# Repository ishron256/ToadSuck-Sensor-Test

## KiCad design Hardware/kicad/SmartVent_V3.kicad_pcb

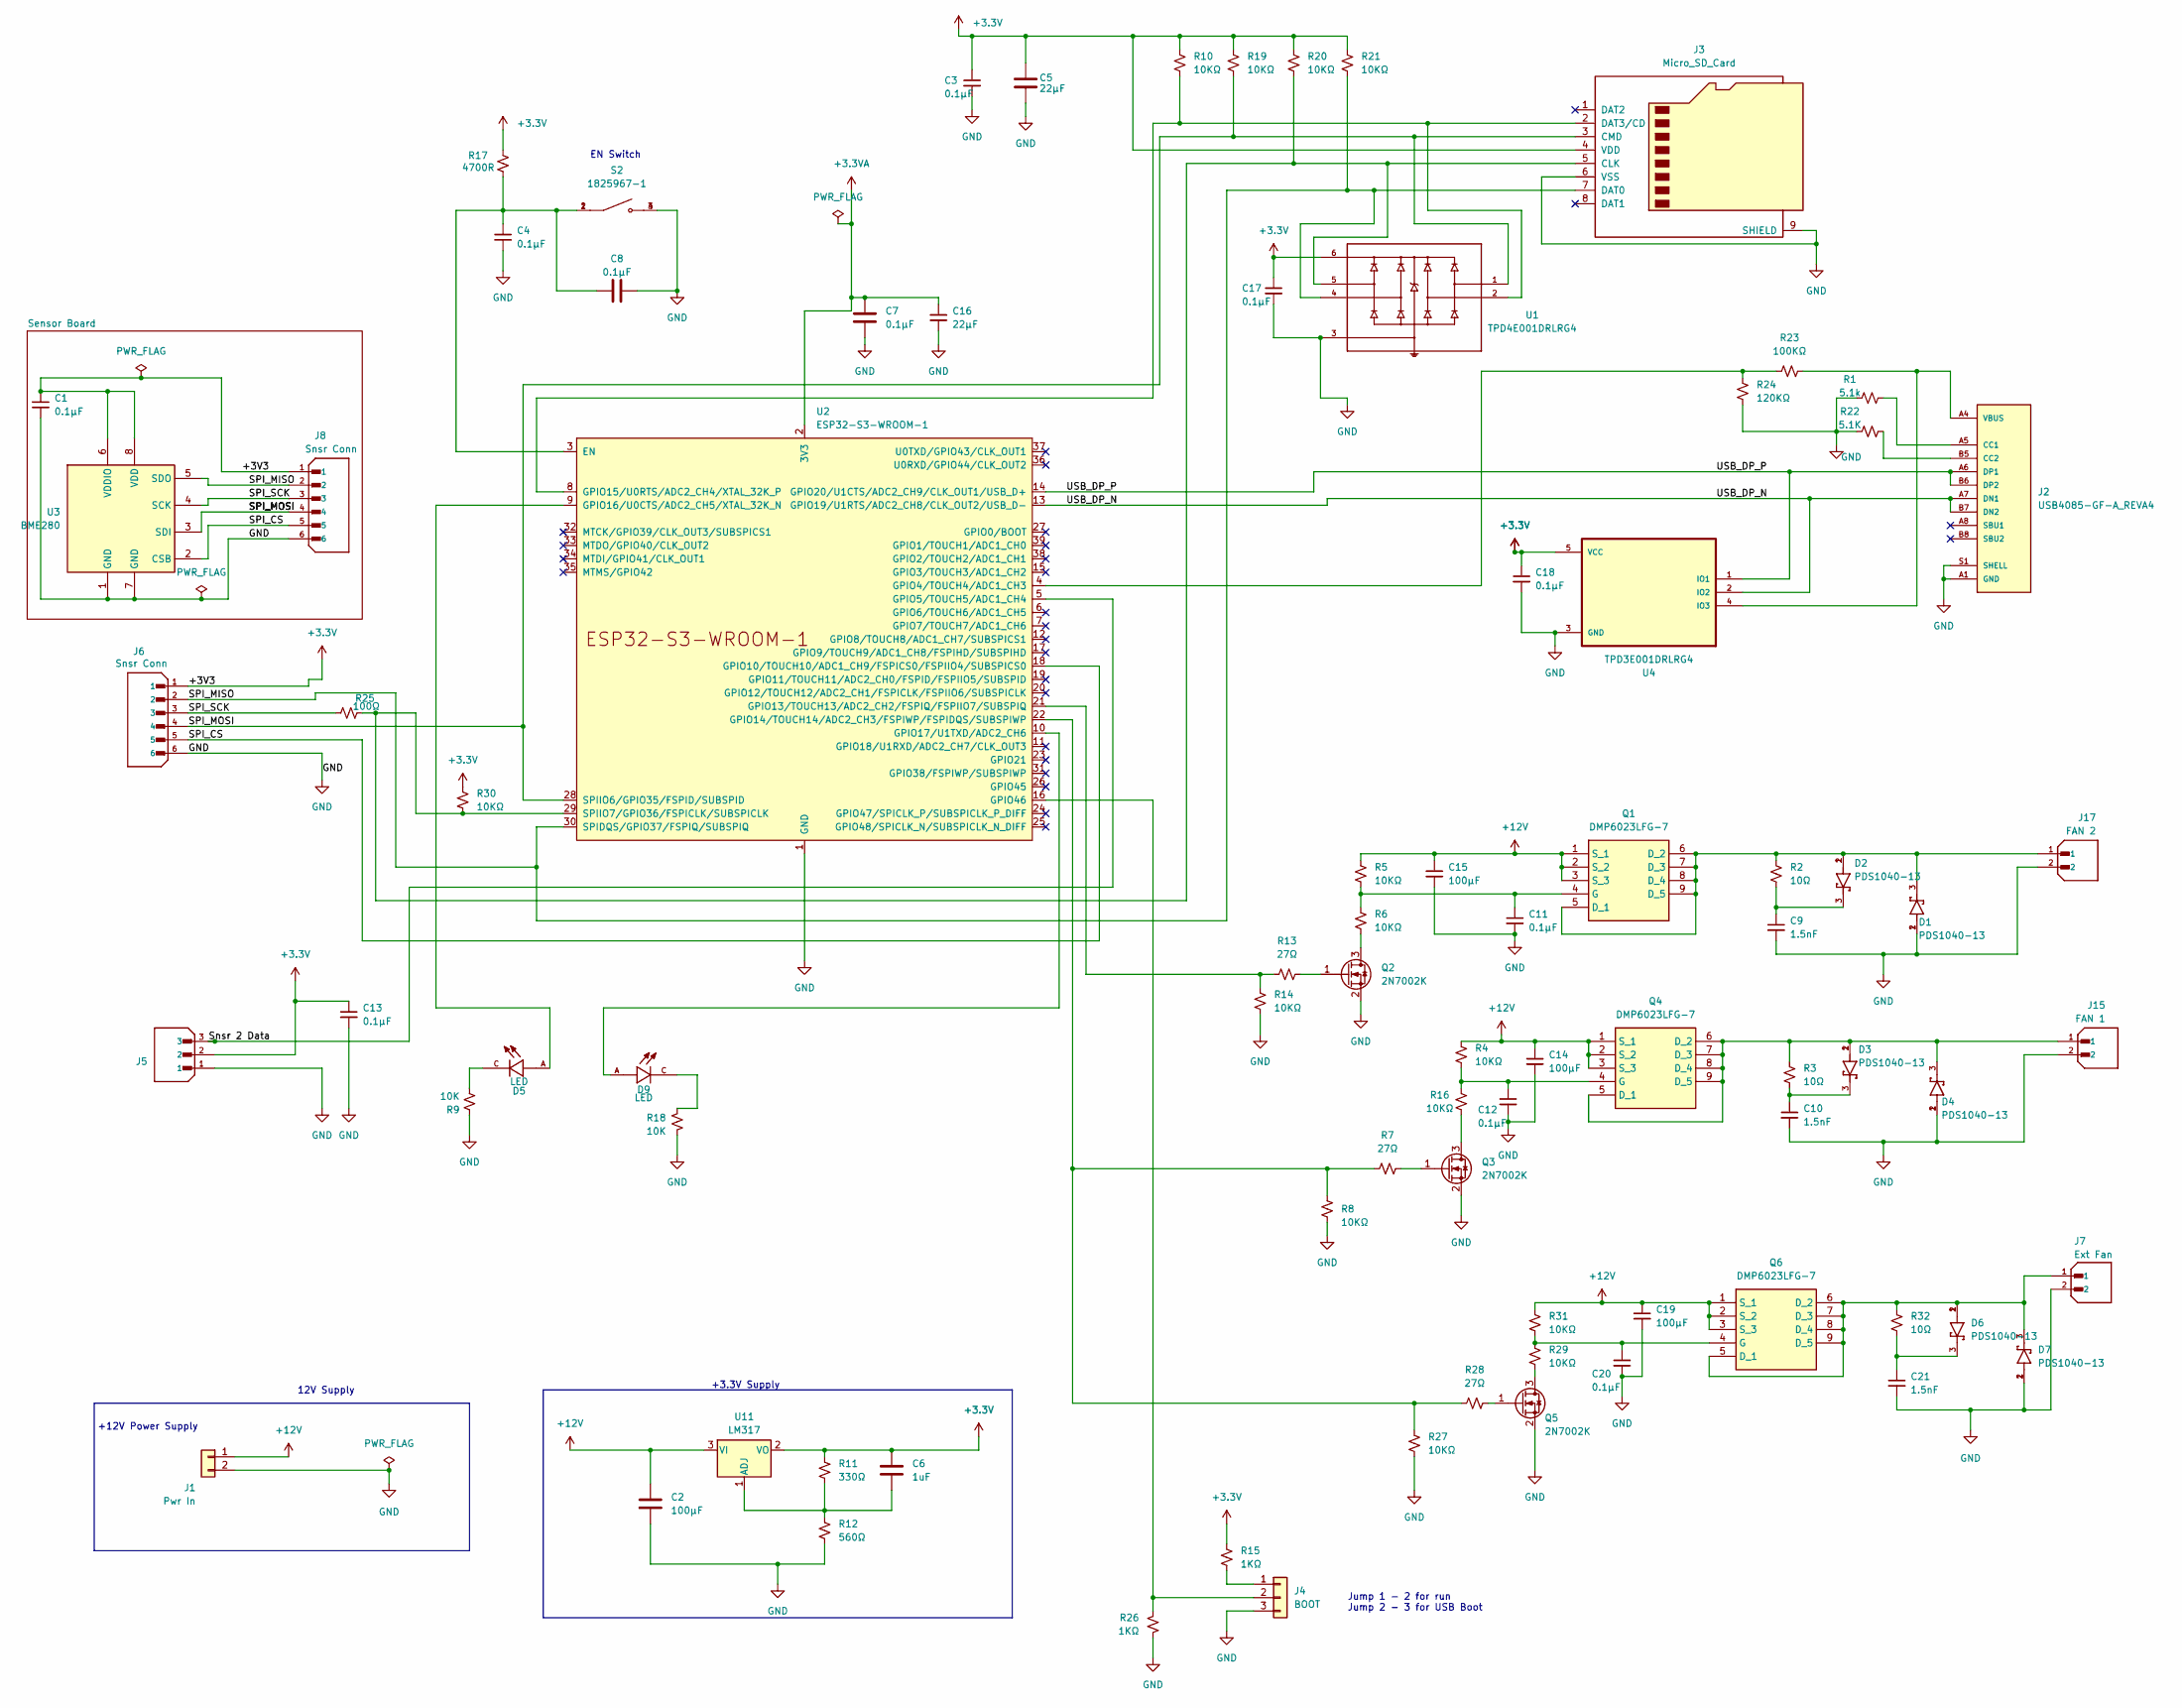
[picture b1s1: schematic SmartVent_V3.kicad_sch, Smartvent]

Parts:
C1, C4, C7, C8, C11, C12, C13, C17, C18, C20: 0.1µF; C_0603_1608Metric
C2, C14, C15, C19: 100µF; SmartVent_Footprint_Capacitor_SMDC_0603_1608Metric_Kyocera_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
C3: 0.1µF; C_0603_1608Metric; Voltage 6.3V; Tolerance 20%
C5, C16: 22µF; C_0603_1608Metric
C6: 1uF; SmartVent_Footprint_C_0603_1608Metric_Yageo_CC0603MRX5R6BB1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
C9, C10, C21: 1.5nF; C_0603_1608Metric
D1, D2, D3, D4, D6, D7: PDS1040-13; DIO_PDS1040-13; PARTREV 13
D5, D9: LED; LED_SML-D12V1WT86; PARTREV 007
J1: Pwr In; Molex_Nano-Fit_105309-xx02_1x02_P2.50mm_Vertical
J2: USB4085-GF-A_REVA4; GCT_USB4085-GF-A_REVA4; PARTREV A4
J3: Micro_SD_Card; SmartVent_Footprint_microSD_HC_Wuerth_693072010801
J4: BOOT; JST_EH_B3B-EH-A_1x03_P2.50mm_Vertical
J5: B3B-XH-A; JST_B3B-XH-A; PARTREV 7/4/21
J6, J8: Snsr Conn; JST_B6B-XH-A_LF__SN_; PARTREV 7/4/21
J7: Ext Fan; JST_B2B-XH-A; PARTREV N/A
J15: FAN 1; JST_B2B-XH-A; MPN B2B-XH-A(LF)(SN); Digi-Key_PN 455-2247-ND
J17: FAN 2; JST_B2B-XH-A; MPN B2B-XH-A(LF)(SN); Digi-Key_PN 455-2247-ND
Q1, Q4, Q6: DMP6023LFG-7; DMP4013LFG7; Mouser Part Number 621-DMP6023LFG-7
Q2, Q3, Q5: 2N7002K; SOT-23
R1: 5.1k; R_0603_1608Metric
R2, R3, R32: 10Ω; R_0603_1608Metric
R4, R5, R6, R8, R10, R14, R16, R19, R20, R21, R27, R29, R30, R31: 10KΩ; R_0603_1608Metric
R7, R13, R28: 27Ω; R_0603_1608Metric
R9, R18: 10K; R_0603_1608Metric
R11: 330Ω; R_0603_1608Metric
R12: 560Ω; R_0603_1608Metric
R15, R26: 1KΩ; R_0603_1608Metric
R17: 4700R; R_0603_1608Metric
R22: 5.1K; R_0603_1608Metric
R23: 100KΩ; R_0603_1608Metric
R24: 120KΩ; R_0603_1608Metric
R25: 100Ω; R_0603_1608Metric
S2: 1825967-1; SW_1825967-1; PARTREV E
U1: TPD4E001DRLRG4; SOTFL50P160X60-6N; MPN SDA004-7
U2: ESP32-S3-WROOM-1; XCVR_ESP32-S3-WROOM-1-N4_EP
U3: BME280; Bosch_LGA-8_2.5x2.5mm_P0.65mm_ClockwisePinNumbering
U4: TPD3E001DRLRG4; SOT50P160X60-5N
U11: LM317; SOT-223-3_TabPin2

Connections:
+3.3V: C1.1, C3.1, C5.1, C6.1, C13.1, C17.1, C18.1, J3.4 (VDD), J5.2, J6.1, J8.1, R10.1, R11.1, R15.1, R17.2, R19.1, R20.1, R21.1, R30.1, U1.6, U3.6 (VDDIO), U3.8 (VDD), U4.5 (VCC), U11.2 (VO)
+3.3VA: C7.1, C16.1, U2.2 (3V3)
+12V: C2.1, C14.1, C15.1, C19.1, J1.1, Q1.1 (S_1), Q1.2 (S_2), Q1.3 (S_3), Q4.1 (S_1), Q4.2 (S_2), Q4.3 (S_3), Q6.1 (S_1), Q6.2 (S_2), Q6.3 (S_3), R4.1, R5.1, R31.1, U11.3 (VI)
/SPI_CS: J6.5, J8.5, U2.18 (GPIO10/TOUCH10/ADC1_CH9/FSPICS0/FSPIIO4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), U3.2 (CSB)
/SPI_MISO: J3.7 (DAT0), J6.2, J8.2, R21.2, U1.4, U2.30 (SPIDQS/GPIO37/FSPIQ/SUBSPIQ), U3.5 (SDO)
/SPI_SCK: J6.3, J8.3, R25.2, U3.4 (SCK)
/Snsr 2 Data: J5.3, U2.5 (GPIO5/TOUCH5/ADC1_CH4)
/USB_DP_N: J2.A7 (DN1), J2.B7 (DN2), U2.13 (GPIO19/U1RTS/ADC2_CH8/CLK_OUT2/USB_D-), U4.2 (IO2)
/USB_DP_P: J2.A6 (DP1), J2.B6 (DP2), U2.14 (GPIO20/U1CTS/ADC2_CH9/CLK_OUT1/USB_D+), U4.1 (IO1)
GND: C1.2, C2.2, C3.2, C4.2, C5.2, C7.2, C8.1, C9.2, C10.2, C11.2, C12.2, C13.2, C14.2, C15.2, C16.2, C17.2, C18.2, C19.2, C20.2, C21.2, D1.1, D1.2, D4.1, D4.2, D7.1, D7.2, J1.2, J2.A1 (GND), J2.A12 (GND), J2.B1 (GND), J2.B12 (GND), J2.S1 (SHELL), J2.S2 (SHELL), J2.S3 (SHELL), J2.S4 (SHELL), J3.6 (VSS), J3.9 (SHIELD), J4.3, J5.1, J6.6, J7.2, J8.6, J15.2, J17.2, Q2.2 (S), Q3.2 (S), Q5.2 (S), R1.2, R8.2, R9.1, R12.2, R14.2, R18.2, R22.2, R24.2, R26.2, R27.2, S2.3, S2.4, U1.3, U2.1 (GND), U2.40 (GND), U2.41 (GND), U3.1 (GND), U3.7 (GND), U4.3 (GND)
unnamed: C9.1, D2.3, R2.2
unnamed: C10.1, D3.3, R3.2
unnamed: C21.1, D6.3, R32.2
unnamed: D5.C, R9.2
unnamed: D9.C, R18.1
unnamed: J2.A5 (CC1), R1.1
unnamed: J2.B5 (CC2), R22.1
unnamed: J3.5 (CLK), R20.2, R25.1, R30.2, U1.5, U2.29 (SPIIO7/GPIO36/FSPICLK/SUBSPICLK)
unnamed: J3.2 (DAT3/CD), R10.2, U1.2, U2.8 (GPIO15/U0RTS/ADC2_CH4/XTAL_32K_P)
unnamed: J4.1, R15.2
unnamed: J4.2, R26.1, U2.16 (GPIO46)
unnamed: D1.3, D2.1, D2.2, J17.1, Q1.5 (D_1), Q1.6 (D_2), Q1.7 (D_3), Q1.8 (D_4), Q1.9 (D_5), R2.1
unnamed: C11.1, Q1.4 (G), R5.2, R6.1
unnamed: Q2.3 (D), R6.2
unnamed: Q2.1 (G), R13.2
unnamed: Q3.3 (D), R16.1
unnamed: Q3.1 (G), R7.2
unnamed: D3.1, D3.2, D4.3, J15.1, Q4.5 (D_1), Q4.6 (D_2), Q4.7 (D_3), Q4.8 (D_4), Q4.9 (D_5), R3.1
unnamed: C12.1, Q4.4 (G), R4.2, R16.2
unnamed: Q5.3 (D), R29.2
unnamed: Q5.1 (G), R28.1
unnamed: D6.1, D6.2, D7.3, J7.1, Q6.5 (D_1), Q6.6 (D_2), Q6.7 (D_3), Q6.8 (D_4), Q6.9 (D_5), R32.1
unnamed: C20.1, Q6.4 (G), R29.1, R31.2
unnamed: C4.1, C8.2, R17.1, S2.1, S2.2, U2.3 (EN)
unnamed: R23.1, R24.1, U2.4 (GPIO4/TOUCH4/ADC1_CH3)
unnamed: R13.1, R14.1, U2.21 (GPIO13/TOUCH13/ADC2_CH2/FSPIQ/FSPIIO7/S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)
unnamed: R7.1, R8.1, R27.1, R28.2, U2.22 (GPIO14/TOUCH14/ADC2_CH3/FSPIWP/FSPIDQS/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)
unnamed: D5.A, U2.9 (GPIO16/U0CTS/ADC2_CH5/XTAL_32K_N)
unnamed: D9.A, U2.10 (GPIO17/U1TXD/ADC2_CH6)
unnamed: C6.2, R11.2, R12.1, U11.1 (ADJ)
VBUS: J2.A4 (VBUS), J2.A9 (VBUS), J2.B4 (VBUS), J2.B9 (VBUS), R23.2, U4.4 (IO3)

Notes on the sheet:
Jump 1 - 2 for run Jump 2 - 3 for USB Boot
12V Supply
+12V Power Supply
EN Switch
+3.3V Supply

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
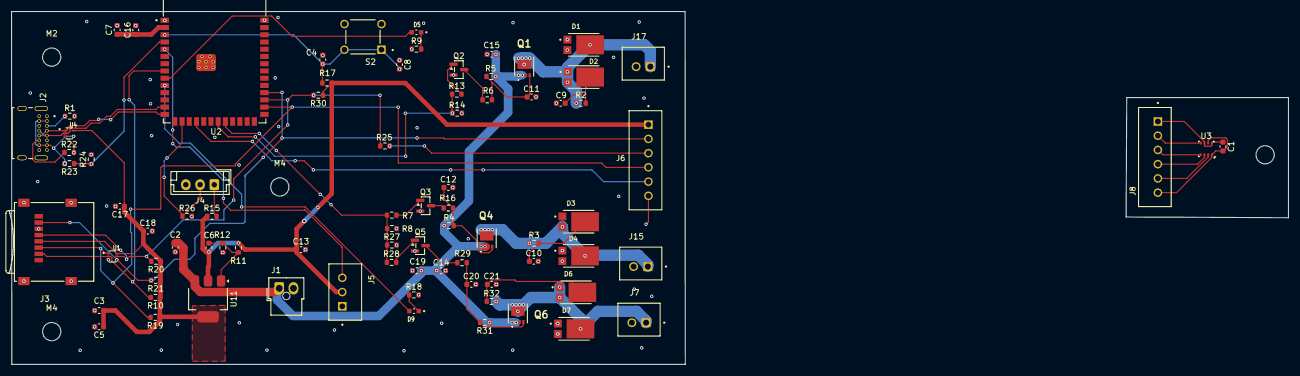
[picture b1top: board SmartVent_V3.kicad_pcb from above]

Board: 4 copper layers, 118.3 x 61.9 mm, 87 parts (0 on the bottom side), 43 nets.

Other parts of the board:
M1, M2, M4, M4#2: MountingHole_3.2mm_M3

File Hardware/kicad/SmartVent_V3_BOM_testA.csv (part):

,Value,Datasheet,Footprint,Qty,DNP,Comment,Digi-Key_PN,Manufacturer_Name,Manufacturer_Part_Number,Snaoeda Link,SnapEDA_Link,Snapeda Link,Description
"C1,C3,C4,C7,C8,C11,C12,C13,C17,C18,C20",0.1 µF,https://www.snapeda.com/parts/0603ZD106KAT2A/AVX/datasheet/,Capacitor_SMD:C_0603_1608Metric,11,,,,AVX,08055C104KAT4A,https://www.snapeda.com/parts/06035C104MAT4A/KYOCERA%20AVX/v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,https://www.snapeda.com/parts/CC0603MRX5R6BB105/Yageo/view-p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,https://www.snapeda.com/parts/0603ZD106KAT2A/AVX/view-part/?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,"Unpolarized capacitor,Unpolarized capacitor, small symbol"
"C2,C14,C15,C19",100 µF,https://www.snapeda.com/parts/06035C104MAT4A/KYOCERA%20AVX/d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,SmartVent_Footprints:SmartVent_Footprint_Capacitor_SMDC_0603_1608Metric_Kyocera_06035C104MAT4A,4,,,,,,,,https://www.snapeda.com/parts/06035C104MAT4A/KYOCERA%20AVX/v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,"Unpolarized capacitor,Unpolarized capacitor, small symbol"
"C5,C16",22 µF,https://www.snapeda.com/parts/06035C104MAT4A/KYOCERA%20AVX/d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,Capacitor_SMD:C_0603_1608Metric,2,,,,AVX,06034D226MAT2A,,,https://www.snapeda.com/parts/06035C104MAT4A/KYOCERA%20AVX/v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,"Unpolarized capacitor,Unpolarized capacitor, small symbol"
C6,1uF,https://www.snapeda.com/parts/CC0603MRX5R6BB105/Yageo/datasheet/,SmartVent_Footprints:SmartVent_Footprint_C_0603_1608Metric_Yageo_CC0603MRX5R6BB105,1,,,,Yageo,CC0603MRX5R6BB105,,https://www.snapeda.com/parts/CC0603MRX5R6BB105/Yageo/view-p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,,Unpolarized capacitor
"C9,C10,C21",1.5nF,https://www.snapeda.com/parts/06034D155MAT2A/AVX/datasheet/,Capacitor_SMD:C_0603_1608Metric,3,,,,,,,,,"Unpolarized capacitor, small symbol"
"D1,D2,D3,D4,D6,D7",PDS1040-13,https://www.snapeda.com/parts/PDS1040-13/Diodes%20Inc./datasheet/,PDS1040-13:DIO_PDS1040-13,6,,,,,,,https://www.snapeda.com/parts/PDS1040-13/Diodes+Inc./view-pa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,,Diode Schottky 40V 10A 3Pin PowerDI 5 | Diodes Inc PDS1040-13
"D5,D9",LED,https://www.snapeda.com/parts/SMLE12BC7TT86/Rohm/datasheet/,SML-D12V1WT86:LED_SML-D12V1WT86,2,,,,,,,https://www.snapeda.com/parts/SMLD12V1WT86/Rohm/view-part/?ref=snap,,Red 630nm LED Indication - Discrete 2.2V 0603 (1608 Metric)
J1,Pwr In,https://www.molex.com/en-us/products/part-detail/1053092102?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,Connector_Molex:Molex_Nano-Fit_105309-xx02_1x02_P2.50mm_Vertical,1,,,,,,,,,"Generic connector, single row, 01x02, script generated (kicad-library-utils/schlib/autogen/connector/)"
J2,USB4085-GF-A_REVA4,https://www.snapeda.com/parts/USB4085-GF-A/Global%20Connecto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,USB4085-GF-A_REVA4:GCT_USB4085-GF-A_REVA4,1,,,,,,,https://www.snapeda.com/parts/USB4085-GF-A/Global+Connector+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,,"USB-C (USB TYPE-C) USB 2.0 Receptacle Connector 24 (16+8 Dummy) Position Through Hole, Right Angle, low cost, 3.46mm profile, 16 pin, horizontal, Top mount"
J3,Micro_SD_Card,https://www.we-online.com/components/products/datasheet/6930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,SmartVent_Footprints:SmartVent_Footprint_microSD_HC_Wuerth_693072010801,1,,,,,,,,,Micro SD Card Socket
J4,BOOT Jumper,http://www.jst-mfg.com/product/pdf/eng/eXH.pdf,Connector_JST:JST_EH_B3B-EH-A_1x03_P2.50mm_Vertical,1,,,,,,,,,"Generic connector, single row, 01x03, script generated (kicad-library-utils/schlib/autogen/connector/)"
J5,B3B-XH-A,https://www.snapeda.com/parts/B3B-XH-A/JST%20Sales/datasheet/,B3B-XH-A:JST_B3B-XH-A,1,,,,,,,https://www.snapeda.com/parts/B3B-XH-A/JST/view-part/?ref=snap,,Connector Header Through Hole 3 position 0.098 (2.50mm)
"J6,J8",Snsr Conn,https://www.snapeda.com/parts/B6B-XH-A(LF)(SN)/JST%20Sales%2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,B6B-XH-A_LF__SN_:JST_B6B-XH-A_LF__SN_,2,,,,,,,https://www.snapeda.com/parts/B6B-XH-A(LF)(SN)/JST/view-part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,,Connector Header Through Hole 6 position 0.098 (2.50mm)
J7,Ext Fan,http://www.jst-mfg.com/product/pdf/eng/eXH.pdf,B2B_XH_A:JST_B2B-XH-A,1,,,,,,,,,CONN HEADER VERT 2POS 2.5MM
J15,FAN 1,http://www.jst-mfg.com/product/pdf/eng/eXH.pdf,B2B_XH_A:JST_B2B-XH-A,1,,,455-2247-ND,,,,,,CONN HEADER VERT 2POS 2.5MM
J17,FAN 2,http://www.jst-mfg.com/product/pdf/eng/eXH.pdf,B2B_XH_A:JST_B2B-XH-A,1,,,455-2247-ND,,,,,,CONN HEADER VERT 2POS 2.5MM
"Q1,Q4,Q6",DMP6023LFG-7,https://www.diodes.com//assets/Datasheets/DMP6023LFG.pdf,LIB_DMP6023LFG-7:DMP4013LFG7,3,,,,Diodes Incorporated,DMP6023LFG-7,,,,MOSFET P-Ch 60V Enh Mode 20Vgs 53.1nC 2569pF
"Q2,Q3,Q5",2N7002K,https://www.diodes.com/assets/Datasheets/ds30896.pdf,Package_TO_SOT_SMD:SOT-23,3,,,,,,,,,"0.38A Id, 60V Vds, N-Channel MOSFET, SOT-23"
R1,5.1k Ohm,https://www.snapeda.com/parts/ERA-3VEB5101V/Panasonic%20Elec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,Resistor_SMD:R_0603_1608Metric,1,,,,,,,,https://www.snapeda.com/parts/ERA-3VEB5101V/Panasonic%20Elec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,"Resistor, small US symbol"
"R2,R3,R32",10 Ohm,"https://www.snapeda.com/parts/RCP0603B10R0JS2/Vishay/datasheet/,https://www.vishay.com/docs/20035/dcrcwe3.pdf",Resistor_SMD:R_0603_1608Metric,3,,,,,,,,,"Resistor,Resistor, small US symbol"
"R4,R5,R6,R8,R10,R14,R16,R19,R20,R21,R27,R29,R30,R31",10K Ohm,https://www.snapeda.com/parts/CRGCQ0805F10K/TE%20Connectivit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,Resistor_SMD:R_0603_1608Metric,14,,,,,,,https://www.snapeda.com/parts/CRGCQ0603F10K/TE%20Connectivit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,,"Resistor, small US symbol"
"R7,R13,R28",27 Ohm,https://www.snapeda.com/parts/CRCW060327R0FKEA/Vishay%20Dale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,Resistor_SMD:R_0603_1608Metric,3,,,,,,,,,"Resistor, small US symbol"
"R9,R18",10K Ohm,https://www.snapeda.com/parts/CRGCQ0603F10K/TE%20Connectivit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,Resistor_SMD:R_0603_1608Metric,2,,,,,,,https://www.snapeda.com/parts/CRGCQ0603F10K/TE%20Connectivit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,,"Resistor, small US symbol"
R11,330 Ohm,https://www.snapeda.com/parts/ERJ-S03J331V/Panasonic/datasheet/,Resistor_SMD:R_0603_1608Metric,1,,,,,,,https://www.snapeda.com/parts/ERJ-S03J331V/Panasonic/view-pa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,,"Resistor, small US symbol"
R12,560 Ohm,https://www.snapeda.com/parts/ERJ-8ENF5600V/Panasonic/datasheet/,Resistor_SMD:R_0603_1608Metric,1,,,,,,,https://www.snapeda.com/parts/ERA-3VEB5600V/Panasonic%20Elec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,,"Resistor, small US symbol"
"R15,R26",1K Ohm,https://www.snapeda.com/parts/MCT06030E1001BP500/Vishay/view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,Resistor_SMD:R_0603_1608Metric,2,,,,,,,,,"Resistor, small US symbol"
R17,4700 Ohm,https://www.snapeda.com/parts/ERJ-S03F4700V/Panasonic/datasheet/,Resistor_SMD:R_0603_1608Metric,1,,,,,,,https://www.snapeda.com/parts/RSF1JB1K00/SEI%20Stackpole%20E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,,"Resistor, small US symbol"
R22,5.1k Ohm,https://www.snapeda.com/parts/AC0603FR-135K1L/Yageo/view-par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,Resistor_SMD:R_0603_1608Metric,1,,,,,,,,,"Resistor, small US symbol"
R23,100K Ohm,https://www.snapeda.com/parts/RT0603BRB07100KL/Yageo/datasheet/,Resistor_SMD:R_0603_1608Metric,1,,,,,,,,,"Resistor, small US symbol"
R24,120K Ohm,https://www.snapeda.com/parts/ERJPA3D1203V/Panasonic/datasheet/,Resistor_SMD:R_0603_1608Metric,1,,,,,,,,,"Resistor, small US symbol"
R25,100 Ohm,https://www.snapeda.com/parts/RT0603BRB07100KL/Yageo/datasheet/,Resistor_SMD:R_0603_1608Metric,1,,,,,,,,,"Resistor, small US symbol"
S2,1825967-1,https://www.snapeda.com/parts/1825967-1/TE%20Connectivity/da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,1825967-1:SW_1825967-1,1,,1825967-1,,,,,https://www.snapeda.com/parts/1825967-1/TE+Connectivity+%252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,,Switch Tactile OFF (ON) SPST Round Button PC Pins 0.05A 24VDC 1.57N Thru-Hole
U1,TPD4E001DRLRG4,https://www.snapeda.com/parts/SDA004-7/Diodes%20Inc./datasheet/,TPD4E001DRLRG4:SOTFL50P160X60-6N,1,,,,,,,https://www.snapeda.com/parts/TPD4E001DRLRG4/Texas+Instrumen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,,Low-capacitance 4-channel +/-15-k-V ESD protection array for high-speed data interfaces 6-SOT-5X3 -40 to 85
U2,ESP32-S3-WROOM-1,https://www.espressif.com/sites/default/files/documentation/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,Library_2:XCVR_ESP32-S3-WROOM-1-N4_EP,1,,,,,,,,,"2.4 GHz WiFi (802.11 b/g/n) and Bluetooth Â® 5 (LE) module Built around ESP32S3 series of SoCs, Xtensa Â® dualcore 32bit LX7 microprocessor Flash up to 16 MB, PSRAM up to 8 MB 36 GPIOs, rich set of peripherals Onboard PCB antenna"
U3,BME280,https://www.bosch-sensortec.com/media/boschsensortec/downloa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,Package_LGA:Bosch_LGA-8_2.5x2.5mm_P0.65mm_ClockwisePinNumbering,1,,,,,,,,,"3-in-1 sensor, humidity, pressure, temperature, I2C and SPI interface, 1.71-3.6V, LGA-8"
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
